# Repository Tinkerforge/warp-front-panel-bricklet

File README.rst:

WARP Front Panel Bricklet
=========================

**This Bricklet is currently in development.**

This repository contains the firmware source code and the hardware design
files. The documentation generator configs can be found at
https://github.com/Tinkerforge/generators

Repository Overview
-------------------

.. DO NOT EDIT THIS OVERVIEW MANUALLY! CHANGE https://github.com/Tinkerforge/esp32-firmware/repo_overview.rst AND COPY THAT BLOCK INTO ALL REPOS LISTED BELOW. TODO: AUTOMATE THIS

Software
~~~~~~~~
- `esp32-firmware <https://github.com/Tinkerforge/esp32-firmware>`__  **Please report any issues concerning WARP hard- and software here!** Source code of the ESP32 firmware shared between all WARP Chargers and Energy Managers

- `tfjson <https://github.com/Tinkerforge/tfjson>`__ SAX style JSON serializer and deserializer
- `tfmodbustcp <https://github.com/Tinkerforge/tfmodbustcp>`__ Modbus TCP server and client implementation
- `tfocpp <https://github.com/Tinkerforge/tfocpp>`__ OCPP 1.6 implementation
- `tftools <https://github.com/Tinkerforge/tftools>`__ Miscellaneous tools and helpers

- `esp32-remote-access <https://github.com/Tinkerforge/esp32-remote-access>`__ Source code of the my.warp-charger.com remote access server

- `warp-charger <https://github.com/Tinkerforge/warp-charger>`__ The source code of (docs.)warp-charger.com and the printed manual, released firmwares, datasheets and documents, as well as some tools and hardware design files
- `api.warp-charger.com <https://github.com/Tinkerforge/api.warp-charger.com>`__ Serves APIs that are used by WARP Chargers to obtain relevant public information like day ahead prices
- `vislog.warp-charger.com <https://github.com/Tinkerforge/vislog.warp-charger.com>`__ Visualizes WARP Charger logs and EVSE debug protocols
- `dbus-warp-charger <https://github.com/Tinkerforge/dbus-warp-charger>`__ Integrates WARP Chargers into a Victron Energy Venus OS device (e.g. Cerbo GX)

WARP Charger Hardware
~~~~~~~~~~~~~~~~~~~~~~

- `esp32-brick <https://github.com/Tinkerforge/esp32-brick>`__ Hardware design files of the ESP32 Brick
- `evse-bricklet <https://github.com/Tinkerforge/evse-bricklet>`__  Firmware source code and hardware design files of the EVSE Bricklet
- `rs485-bricklet <https://github.com/Tinkerforge/rs485-bricklet>`__ Firmware source code and hardware design files of the RS485 Bricklet

WARP2 Charger Hardware
~~~~~~~~~~~~~~~~~~~~~~

- `esp32-ethernet-brick <https://github.com/Tinkerforge/esp32-ethernet-brick>`__ Hardware design files of the ESP32 Ethernet Brick
- `evse-v2-bricklet <https://github.com/Tinkerforge/evse-v2-bricklet>`__ Firmware source code and hardware design files of the EVSE 2.0 Bricklet
- `nfc-bricklet <https://github.com/Tinkerforge/nfc-bricklet>`__ Firmware source code and hardware design files of the NFC Bricklet

WARP3 Charger Hardware
~~~~~~~~~~~~~~~~~~~~~~

- `warp-esp32-ethernet-brick <https://github.com/Tinkerforge/warp-esp32-ethernet-brick>`__ Hardware design files of the WARP ESP32 Ethernet Brick
- `evse-v3-bricklet <https://github.com/Tinkerforge/evse-v3-bricklet>`__ Firmware source code and hardware design files of the EVSE 3.0 Bricklet
- `nfc-bricklet <https://github.com/Tinkerforge/nfc-bricklet>`__ Firmware source code and hardware design files of the NFC Bricklet

WARP Energy Manager Hardware
~~~~~~~~~~~~~~~~~~~~~~~~~~~~

- `esp32-ethernet-brick <https://github.com/Tinkerforge/esp32-ethernet-brick>`__ Hardware design files of the ESP32 Ethernet Brick
- `warp-energy-manager-bricklet <https://github.com/Tinkerforge/warp-energy-manager-bricklet>`__ Firmware source code and hardware design files of the WARP Energy Manager Bricklet

WARP Energy Manager 2.0 Hardware
~~~~~~~~~~~~~~~~~~~~~~~~~~~~~~~~

- `esp32-ethernet-brick <https://github.com/Tinkerforge/esp32-ethernet-brick>`__ Hardware design files of the ESP32 Ethernet Brick
- `warp-energy-manager-v2-bricklet <https://github.com/Tinkerforge/warp-energy-manager-v2-bricklet>`__ Firmware source code and hardware design files of the WARP Energy Manager 2.0 Bricklet
- `warp-front-panel-bricklet <https://github.com/Tinkerforge/warp-front-panel-bricklet>`__ Firmware source code and hardware design files of the WARP Front Panel Bricklet

Forked/patched projects
~~~~~~~~~~~~~~~~~~~~~~~

- `arduino-esp32 <https://github.com/Tinkerforge/arduino-esp32>`__
- `esp32-arduino-libs <https://github.com/Tinkerforge/esp32-arduino-libs>`__
- `WireGuard-ESP32-Arduino <https://github.com/Tinkerforge/WireGuard-ESP32-Arduino>`__

Repository Content
------------------

software/:
 * examples/: Examples for all supported languages
 * build/: Compiled files
 * src/: Source code of firmware
 * Makefile: Makefile to build project

hardware/:
 * Contains KiCad project files and additionally schematics as PDF

datasheets/:
 * Contains datasheets for sensors and complex ICs that are used

Hardware
--------

The hardware is designed with the open source EDA Suite KiCad
(http://www.kicad.org). Before you are able to open the files,
you have to install the Tinkerforge kicad-libraries
(https://github.com/Tinkerforge/kicad-libraries). You can either clone
them directly in hardware/ or clone them in a separate folder and
symlink them into hardware/
(ln -s kicad_path/kicad-libraries project_path/hardware). After that you
can open the .pro file in hardware/ with KiCad and from there view and
modify the schematics and the PCB layout.

Software
--------

If you want to do your own Brick/Bricklet firmware development we highly
recommend that you use our build environment setup script and read the
tutorial (https://www.tinkerforge.com/en/doc/Tutorials/Tutorial_Build_Environment/Tutorial.html).

To compile the C code we recommend you to install the newest GNU Arm Embedded
Toolchain (https://launchpad.net/gcc-arm-embedded/+download).
You also need to install bricklib2 (https://github.com/Tinkerforge/bricklib2).

You can either clone it directly in software/src/ or clone it in a
separate folder and symlink it into software/src/
(ln -s bricklib_path/bricklib2 project_path/software/src/). Finally make sure to
have CMake installed (http://www.cmake.org/cmake/resources/software.html).

After that you can build the firmware by invoking make in software/.
The firmware (.zbin) can then be found in software/build/ and uploaded
with brickv (click button "Flashing" on start screen).

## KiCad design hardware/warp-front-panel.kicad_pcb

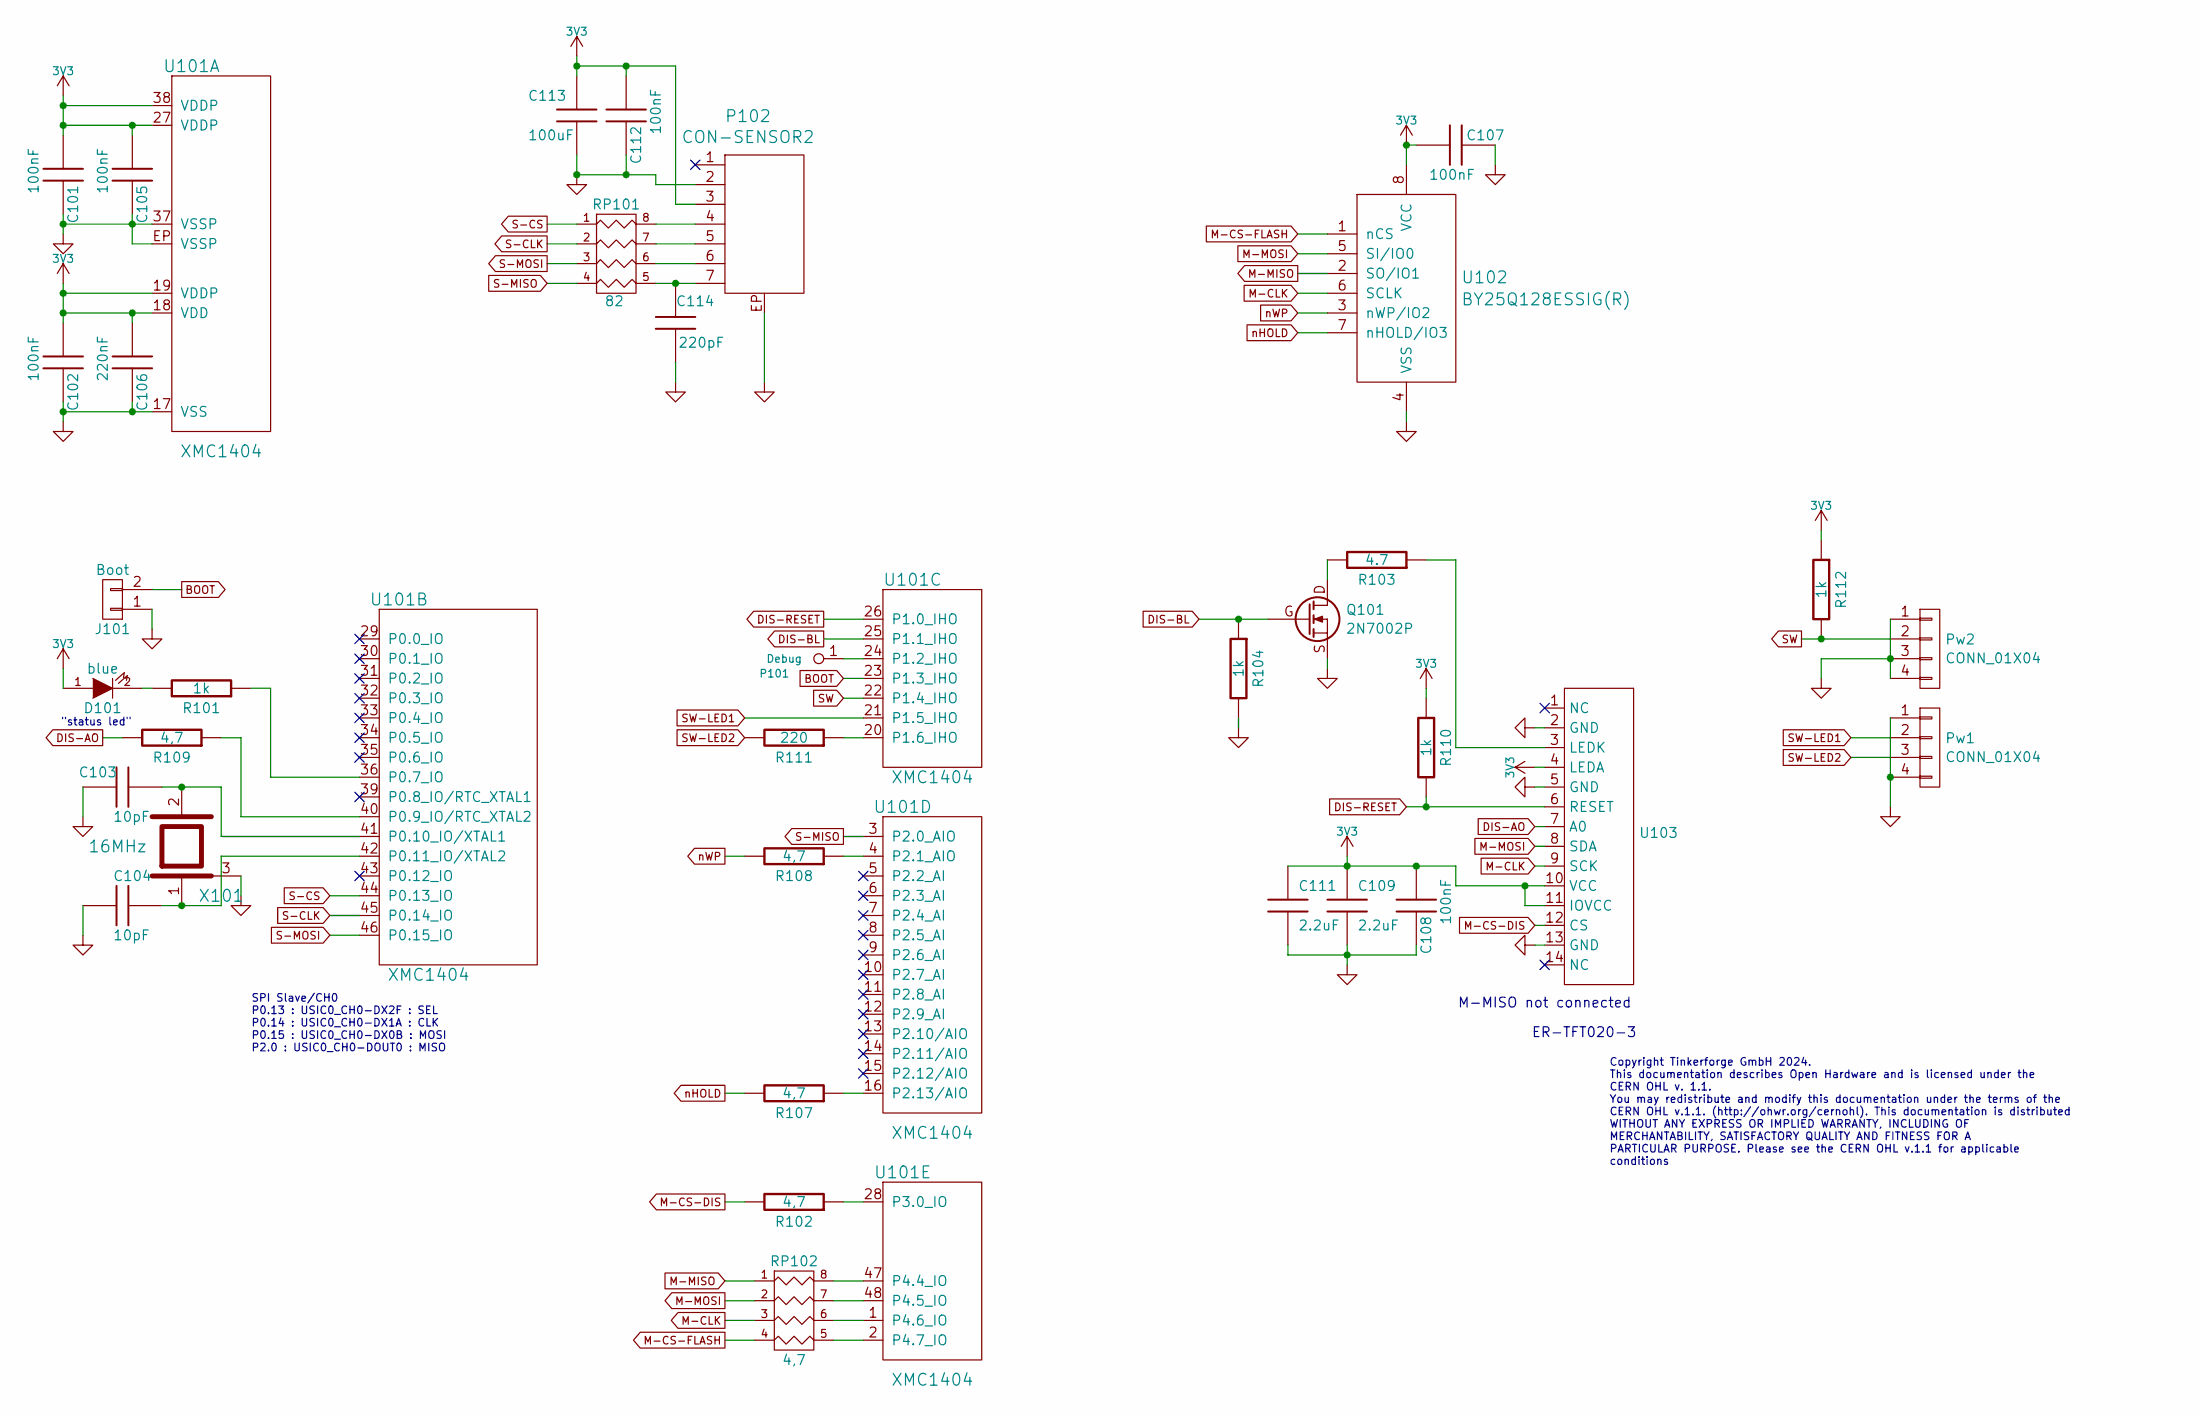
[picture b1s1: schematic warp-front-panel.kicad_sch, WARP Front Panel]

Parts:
C101, C102, C105, C107, C108, C112: 100nF; C0603F
C103, C104: 10pF; C0603F
C106: 220nF; C0603F
C109, C111: 2.2uF; C0603F
C113: 100uF; C1210
C114: 220pF; C0402F
D101: blue; D0603F
J101: Boot; SolderJumper
P101: Debug; TSTP_STL
P102: CON-SENSOR2; CON-SENSOR2_180
Pw1, Pw2: CONN_01X04; pin_array_1x4-P2mm_D1mm
Q101: 2N7002P; SOT23GDS
R101, R104, R110, R112: 1k; R0603F
R102, R107, R108, R109: 4,7; R0603F
R103: 4.7; R0603F
R111: 220; R0603F
RP101: 82; 4X0402
RP102: 4,7; 4X0402
U101: XMC1404; QFN48-EP2
U102: BY25Q128ESSIG(R); SO-8
U103: ZIF_14P_0.5mm
X101: 16MHz; CRYSTAL_3225

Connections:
3V3: C101.1, C102.1, C105.1, C106.1, C107.1, C108.1, C109.1, C111.1, C112.1, C113.1, D101.1 (A), P102.3, R110.1, R112.1, U101.18 (VDD), U101.19 (VDDP), U101.27 (VDDP), U101.38 (VDDP), U102.8 (VCC), U103.4 (LEDA), U103.10 (VCC), U103.11 (IOVCC)
BOOT: J101.2, U101.23 (P1.3_IHO)
DIS-AO: R109.2, U103.7 (A0)
DIS-BL: Q101.G, R104.1, U101.25 (P1.1_IHO)
DIS-RESET: R110.2, U101.26 (P1.0_IHO), U103.6 (RESET)
GND: C101.2, C102.2, C103.2, C104.2, C105.2, C106.2, C107.2, C108.2, C109.2, C111.2, C112.2, C113.2, C114.2, J101.1, P102.2, P102.EP, Pw1.1, Pw1.4, Pw2.1, Pw2.3, Pw2.4, Q101.S, R104.2, U101.17 (VSS), U101.37 (VSSP), U101.EP (VSSP), U102.4 (VSS), U103.2 (GND), U103.5 (GND), U103.13 (GND), X101.3
M-CLK: RP102.3, U102.6 (SCLK), U103.9 (SCK)
M-CS-DIS: R102.2, U103.12 (CS)
M-CS-FLASH: RP102.4, U102.1 (nCS)
M-MISO: RP102.1, U102.2 (SO/IO1)
M-MOSI: RP102.2, U102.5 (SI/IO0), U103.8 (SDA)
unnamed: D101.2 (K), R101.2
unnamed: Q101.D, R103.2
unnamed: P102.4, RP101.8 (R1)
unnamed: P102.5, RP101.7 (R2)
unnamed: P102.6, RP101.6 (R3)
unnamed: C114.1, P102.7, RP101.5 (R4)
unnamed: RP102.8 (R1), U101.47 (P4.4_IO)
unnamed: RP102.7 (R2), U101.48 (P4.5_IO)
unnamed: RP102.6 (R3), U101.1 (P4.6_IO)
unnamed: RP102.5 (R4), U101.2 (P4.7_IO)
unnamed: R101.1, U101.36 (P0.7_IO)
unnamed: R109.1, U101.40 (P0.9_IO/RTC_XTAL2)
unnamed: C103.1, U101.41 (P0.10_IO/XTAL1), X101.2
unnamed: C104.1, U101.42 (P0.11_IO/XTAL2), X101.1
unnamed: P101.1, U101.24 (P1.2_IHO)
unnamed: R111.1, U101.20 (P1.6_IHO)
unnamed: R108.1, U101.4 (P2.1_AIO)
unnamed: R107.1, U101.16 (P2.13/AIO)
unnamed: R102.1, U101.28 (P3.0_IO)
unnamed: R103.1, U103.3 (LEDK)
S-CLK: RP101.2, U101.45 (P0.14_IO)
S-CS: RP101.1, U101.44 (P0.13_IO)
S-MISO: RP101.4, U101.3 (P2.0_AIO)
S-MOSI: RP101.3, U101.46 (P0.15_IO)
SW: Pw2.2, R112.2, U101.22 (P1.4_IHO)
SW-LED1: Pw1.2, U101.21 (P1.5_IHO)
SW-LED2: Pw1.3, R111.2
nHOLD: R107.2, U102.7 (nHOLD/IO3)
nWP: R108.2, U102.3 (nWP/IO2)

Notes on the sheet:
"status led"
SPI Slave/CH0 P0.13 : USIC0_CH0-DX2F : SEL P0.14 : USIC0_CH0-DX1A : CLK P0.15 : USIC0_CH0-DX0B : MOSI P2.0 : USIC0_CH0-DOUT0 : MISO
M-MISO not connected
Copyright Tinkerforge GmbH 2024. This documentation describes Open Hardware and is licensed under the CERN OHL v. 1.1. You may redistribute and modify this documentation under the terms of the CERN OHL v.1.1. (http://ohwr.org/cernohl). This documentation is distributed WITHOUT ANY EXPRESS OR IMPLIE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
ER-TFT020-3

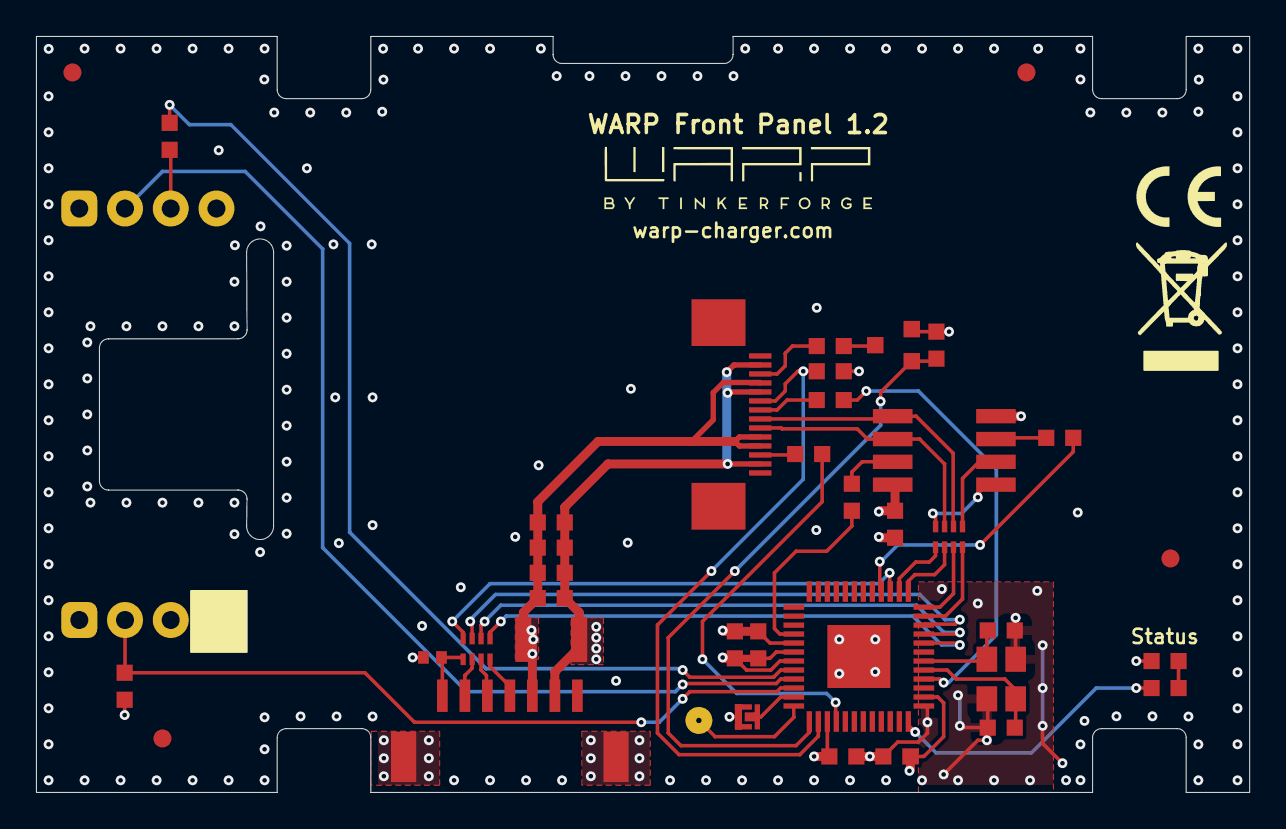
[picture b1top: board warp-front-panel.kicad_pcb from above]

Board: 4 copper layers, 67.4 x 42.0 mm, 42 parts (0 on the bottom side), 40 nets.

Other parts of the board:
Fiducial_Mark: VAL**; Fiducial_Mark
Fiducial_Mark#2, Fiducial_Mark#3, Fiducial_Mark#4: VAL**; Fiducial_Mark
VAL: CE_5mm
VAL#2: WEEE_7mm

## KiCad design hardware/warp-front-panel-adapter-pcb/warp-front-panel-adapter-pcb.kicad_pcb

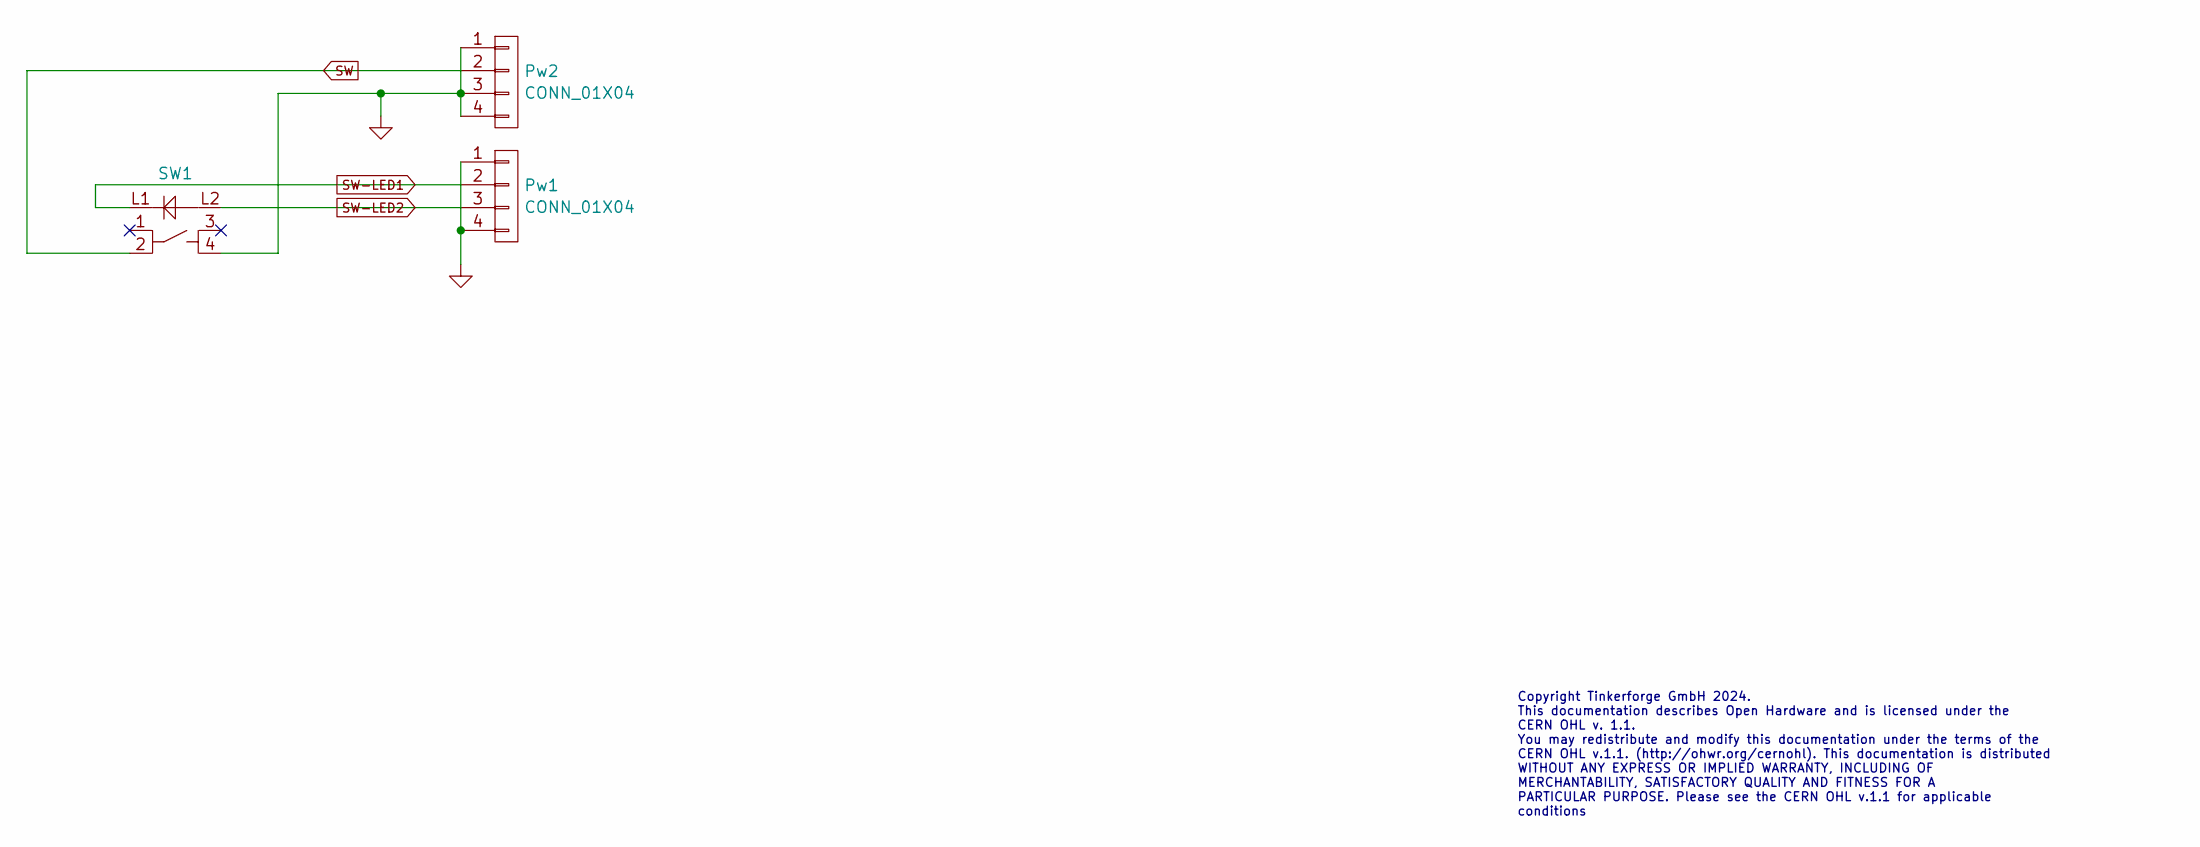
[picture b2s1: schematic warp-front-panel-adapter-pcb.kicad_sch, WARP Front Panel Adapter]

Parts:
Pw1, Pw2: CONN_01X04; pin_array_1x4-P2mm_D1mm
SW1: LED_TACT_SW_THT

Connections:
GND: Pw1.1, Pw1.4, Pw2.1, Pw2.3, Pw2.4, SW1.4
SW: Pw2.2, SW1.2
SW-LED1: Pw1.2, SW1.L1
SW-LED2: Pw1.3, SW1.L2

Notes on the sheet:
Copyright Tinkerforge GmbH 2024. This documentation describes Open Hardware and is licensed under the CERN OHL v. 1.1. You may redistribute and modify this documentation under the terms of the CERN OHL v.1.1. (http://ohwr.org/cernohl). This documentation is distributed WITHOUT ANY EXPRESS OR IMPLIE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

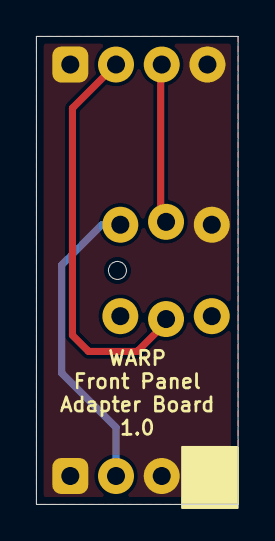
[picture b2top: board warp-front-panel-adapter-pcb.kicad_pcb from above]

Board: 2 copper layers, 11.2 x 26.0 mm, 3 parts (1 on the bottom side), 4 nets.

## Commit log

2024-06-13 Initial commit of autogenerated stub firmware
2024-06-18 add partial prototype
2024-06-21 prototype version
2024-06-28 add schematic
2024-06-28 fix signal directions
2024-06-28 Add ST7789 testing code
2024-06-28 Add datasheets
2024-06-28 Properly initialize ST7789 and add bouncing circle for testing
2024-06-29 Add stub implementation for button and PSRAM
2024-06-29 Fix select mixup
2024-06-29 Use correct select define
2024-06-29 Fix typo
2024-06-29 Use uint32_t for length caluclations
    320*240 > 2**16
2024-06-29 second MISO is unused for now
2024-06-29 Add testing drawings
2024-06-29 Add MISO2 define
2024-06-29 Add API for Flash testing
2024-06-29 Add stub configs
2024-06-29 Add PSRAM datasheet
2024-06-30 Add SPI transceive option for no select and no deselect
2024-06-30 Add 100ms sleep before init
2024-06-30 Use uint32_t for length
2024-06-30 Add basic function to read/write the BY25Q flash
2024-06-30 Add task that reads from BY25Q flash and writes to ST7789 driver
2024-06-30 Remove copied and unused code
2024-06-30 Add test code that can be switched on/off with ifdef
2024-06-30 Add python test scripts
2024-07-02 Add qrcode lib
2024-07-03 Add options to SPI transceive and add erase functions to BY25Q flash
2024-07-03 Force ST7789 to never block the SPI bus completely
    If there is data to write to the by25q, we wait here until it is written.
    This makes sure that there can be at least on write to the by25q per write to the display.
    Otherwise the st7789 could block the SPI bus.
2024-07-03 Add strategic coop_task_yield into QR code calculation
    Calculation now takes 200ms instead of 100ms, but there i a yield
    every 100us or less.
2024-07-03 Use stdbool
2024-07-03 Add coop task include
2024-07-03 Add QR code test
2024-07-03 Add sequences to image test script
2024-07-03 Update bindings
2024-07-03 Add scripts to make font sprites
2024-07-03 Add primitive font rendering support
2024-07-04 Rename FontCharset to FontList
2024-07-04 Add simple sprites helper function
2024-07-10 Make sure space is part of the char table
2024-07-15 Add python scripts to create a flash map and write it to XMC
2024-07-15 Renamte folder font -> fonts
2024-07-15 Add button press with debounce support
    Also include LED testing here for now, will be removed later
2024-07-15 Add front page and qr code page
    this include some initial sprites and fonts for testing
2024-07-15 Split ST7789 driver in driver and display util functions
2024-07-15 Add status bar
2024-07-15 Add font width and height to generator
2024-07-15 Add functions for display and status bar
2024-07-15 Use new display function instead of st7789
2024-07-15 Update generated font list
2024-07-15 Add front page support
2024-07-15 Add temporary test font
2024-07-15 Add status and front page tests
2024-07-15 Mix of tabs/spaces -> spaces only
2024-07-15 Add "end-to-end" font generation for testing different fonts
2024-07-15 Update fonts and font positions
2024-07-15 Change font to DejaVu Sans Mono Bold
2024-07-16 Add common.py
2024-07-16 Update dimensions
2024-07-16 Update fonts and use PX instead of PT for defines
2024-07-16 Update icons sprites and sprite sizes
2024-07-16 Draw line in background
    This is makes testing easier, might be removed again at the end
2024-07-16 Add status bar defines
2024-07-16 Add generated files to gitignore
2024-07-16 Add kicad hardware temp files to gitignore
2024-07-16 Use proper font define for status bar font index
2024-07-16 Add wifi setup page API
2024-07-17 updated design V1.2
2024-07-17 added adapter pcb
2024-07-17 change hole
2024-07-17 improve routing
2024-07-17 visible layers changed
2024-07-17 Add display size defines
2024-07-17 Implement WIFI setup page
2024-07-17 Add support for status bar status text
    Can be used instead of the clock for a title of the page
2024-08-28 new sprites
2024-08-28 Change max text chars from 10 to 6
2024-08-28 Fix pin defines
2024-08-28 Add support for new status bar sprites
2024-08-28 Properly check values of wifi_setup setter
2024-08-28 Add set/get_led_state API functions
2024-08-28 Implement LED API
2024-08-29 Make sure PWM is synced and uses maximum brightness (for yellow color)
2024-08-29 Add new sprites
2024-08-29 Add sprite copy script
2024-08-29 Add and implement API to turn display off/automatic
    In automatic mode it will turn off after 60 minutes and
    enable again on button press.
2024-09-06 changed data resistor values to 4,7Ohm
2024-09-06 Make sure display off/automatic are handled properly
2024-09-11 copy.sh: Rename em_front_panel module to front_panel.
2024-09-13 Update sprites.
2024-09-13 sprites: Fix arrow alignment.
2024-09-14 Remove unused code
2024-09-14 Add startup defaults for LED and wifi setup
2024-09-14 Improve sprites
2024-09-14 Add metadata to flashmap
    Currently includes version, length and checksum, but can
    be extended later on.
2024-09-15 Add and implement get_flash_metadata function
2024-09-16 sprites: Add wallet_dollar
2024-09-16 sprites: Add sprite source SVGs.
    Some are recreated, so they currently don't match the sprites perfectly.
2024-09-16 Make sure backlight is off by default and when display is inactive
    Also turn display on after reset only after first page is drawn.
2024-09-16 Remove unnecessary GPIO_Inits
2024-09-17 Add icon
2024-09-27 Add #pragma once to generated header files
2024-10-15 Hardware: Updated Version number
2024-12-06 Add date and ref for 2.0.0
2025-01-22 Add FlashDataDone callback
2025-01-22 Update changelog
2025-01-22 Add RedrawEverything function
2025-01-22 Combine trim operation with font rendering
2025-01-22 Use all-ones for padding
    Zero bytes are slow to erase and write.
2025-01-23 Fix lost-wakeup issue in redraw handling
    Redraw flags must be reset before drawing so that they can be set again from a background update while the drawing is still ongoing.
2025-01-24 Save Flash map xz-compressed
2025-01-24 Generate Flash metadata constants as unsigned
2025-02-05 Update metadata
2025-02-05 Add release date
2025-02-05 Add ref for 2.0.1
2025-07-16 README: Add repo overview.
2025-10-04 Fix compatibility with new Docker build image (GCC 14.2.1)

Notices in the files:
hardware/warp-front-panel-adapter-pcb/warp-front-panel-adapter-pcb.kicad_pcb:
Licensed under CERN OHL v.1.1
Copyright (©) 2024, B.Nordmeyer
